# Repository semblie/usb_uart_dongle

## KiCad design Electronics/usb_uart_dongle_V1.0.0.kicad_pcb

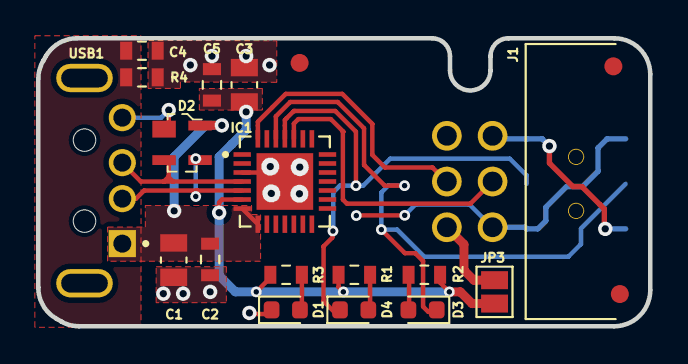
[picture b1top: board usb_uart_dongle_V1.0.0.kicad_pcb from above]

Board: 2 copper layers, 34.0 x 16.0 mm, 21 parts (1 on the bottom side), 16 nets.

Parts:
C1, C3: 10uF_6.3V; 0805
C2, C5: 0.1uF_6.3V; 0603
C4: 1000pF_1kV; 0603
D1, D3: RED; LED_0603_1608Metric
D2: SP0503BAHT; SOT-143-4
D4: GREEN; LED_0603_1608Metric
Fid1, Fid2, Fid3: 1.0mm_Mask_2.0mm; Fiducial_1mm_Mask2mm
IC1: CP2102-GM; QFN-28
J1: 61200621721
JP3: SolderJumper_2_Open; SolderJumper-2_P1.3mm_Open_Pad1.0x1.5mm
R1, R2, R3: 330R; 0603
R4: 1M; 0603
SW1: SS-3390S-L1; SS-33905-1
USB1: 48037-0001; USB_48037-0001

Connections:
+3V3: C3.2, C5.2, IC1.6 (VDD), JP3.1 (A), R1.1, R2.1, R3.1
/D+: D2.2, IC1.4 (D+), USB1.3 (D+)
/D-: D2.3, IC1.5 (D–), USB1.2 (D-)
/RXD: D4.1 (K), IC1.25 (RXD), SW1.2
/TXD: D3.1 (K), IC1.26 (TXD), SW1.5
/UART_PIN_1: J1.6, SW1.1, SW1.6
/UART_PIN_2: J1.2, SW1.3, SW1.4
/VBUS: C1.2, C2.2, D2.4, IC1.7 (REGIN), IC1.8 (VBUS), USB1.1 (VBUS)
/~DTR: IC1.28 (~DTR), J1.3
/~RTS: IC1.24 (~RTS), J1.4
GND: C1.1, C2.1, C3.1, C4.2, C5.1, D1.1 (K), D2.1, IC1.3 (GND), IC1.29 (GND), J1.1, R4.1, USB1.4 (GND)
unnamed: C4.1, R4.2
unnamed: D1.2 (A), R3.2
unnamed: D3.2 (A), R2.2
unnamed: D4.2 (A), R1.2
unnamed: J1.5, JP3.2 (B)

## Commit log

2023-01-19 electronics: add kicad project
2023-01-19 enclosure: add stl file
2023-06-16 V1.0.0
